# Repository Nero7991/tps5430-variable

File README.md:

# TPS5430 Variable or VarTPS

This is a DC-DC Buck converter board based on the TPS5430 from TI with both fixed and variable voltage output options, called VarTPS. The board provides four fixed voltage outputs (1.8V, 3.3V, 5V, 12V) selectable via solder jumpers, plus a variable output mode ranging from 1.24V to 32.4V. Variable voltage control is implemented using two 10-turn potentiometers - a 10kΩ potentiometer for coarse adjustment and a 1kΩ potentiometer for fine adjustment, providing approximately 3mV resolution at low voltages. The design includes reverse polarity protection, overcurrent protection via polyfuse, and accepts input and output throught screw terminals.

## Features

* V<sub>in</sub> = 5.5V..36V
* V<sub>in<sub>min</sub></sub> = 1.15 * V<sub>out</sub> (see Datasheet Section 8.2.1.2.8.1)
* V<sub>in<sub>max</sub></sub> = 8.33 * (V<sub>out</sub> + 0.5) (see Datasheet Section 8.2.1.2.8.1)
* V<sub>out</sub> = 1.8V/3.3V/5V/12V (choose via solder bridge)
* Variable voltage out, adjusted using two 10 turn pot with course and fine adjustments. V<sub>out<sub>adjust</sub></sub> = 1.24V..32.4V (choosen via solder bridge)
* Reverse polarity protection with AO3401A p-MOSFET
* 3A (hold)/6A (trip) polyfuse input protection
* The board can be powered with a 2.1mm/5.5mm "standard" Arduino compatible barrel jack connector.
* Status LED

## Schematic

The design was modified in [KiCAD 9](https://www.kicad.org/) from Max Stabel's [TPS5430 on GitHub](https://github.com/M4a1x/TPS5430) and follows the [TPS5430 datasheet (Section 8.2.1)](https://www.ti.com/lit/ds/symlink/tps5430.pdf) reasonably close in the schmatic as well as the layout (Section 10.2).

Deviations are:

* 2x 100uF tantalum capacitors instead of 1x 220uF, since those are basic parts at JLCPCB
* As suggested a 10uF output bypass capacitor is added
* 4x 10uF input capacitors instead of only 1x
* Multiple output voltage options through increased Inductor (47uH instead of 15uH) and solder jumpers. All outputs should work with the full 3A

## License

Licensed under CERN-OHL-S v2 or any later version. See `LICENSE` for more information.

## Contact

Oren Collaco - [https://orencollaco.com/](https://orencollaco.com) - orencollaco97@gmail.com

Project Link: [https://github.com/Nero7991/tps5430-variable](https://github.com/Nero7991/tps5430-variable)

## Acknowledgements

* [Max Stabel](https://max.stabel.family/), [TPS5430 on GitHub](https://github.com/M4a1x/TPS5430)

* [Philip Salamony](https://philsal.co.uk/) and his [BananaSchplit Project](https://github.com/pms67/BananaSchplit) and [Video](https://www.youtube.com/watch?v=qXWYXxDokv4)
* [ugurozkan52/TPS5430_Power_Module](https://github.com/ugurozkan52/TPS5430_Power_Module) which inspired me to add the output voltage jumpers

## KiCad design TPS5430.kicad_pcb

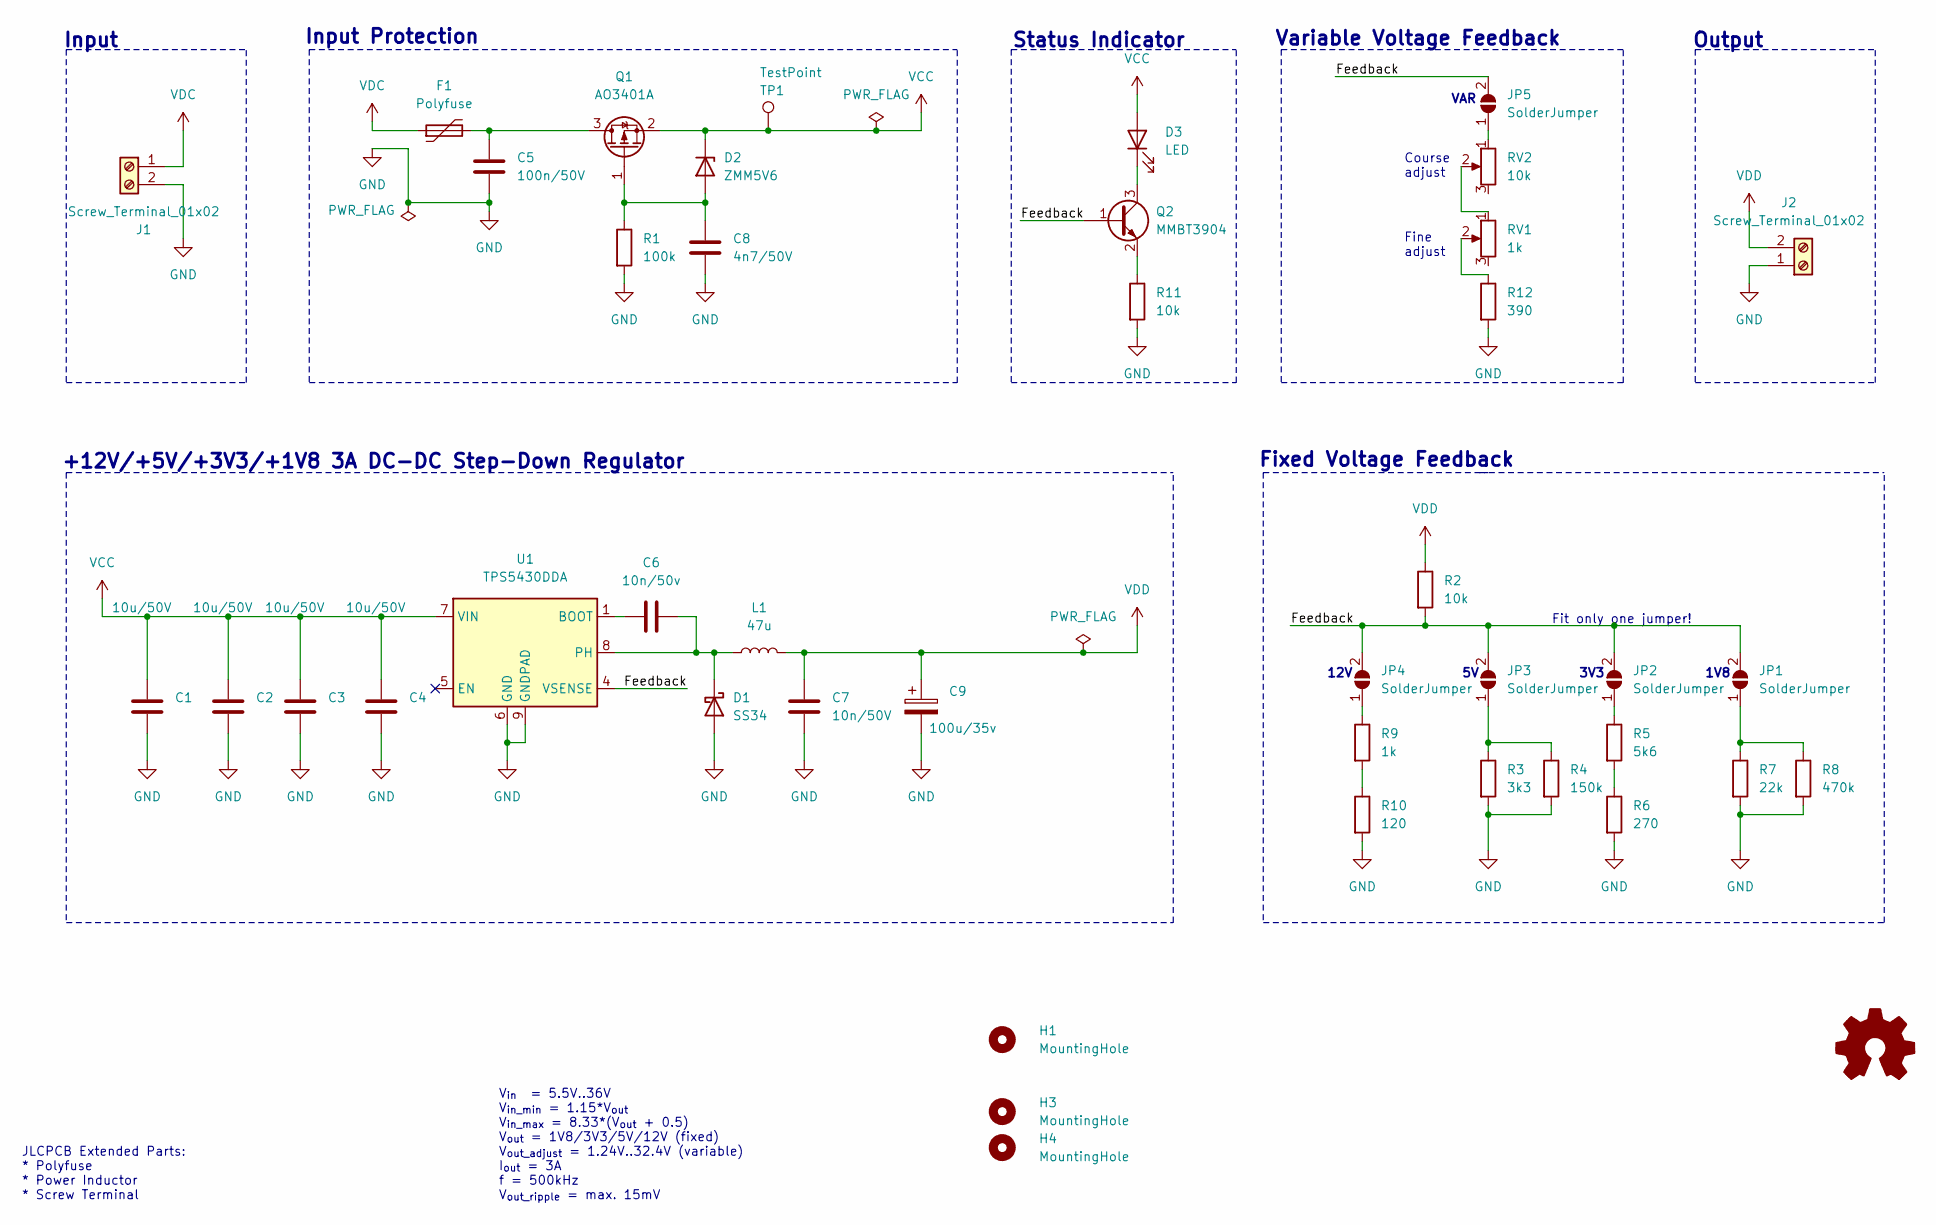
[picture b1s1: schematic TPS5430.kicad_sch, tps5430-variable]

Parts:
C1, C2, C3, C4: 10u/50V; C_1206_3216Metric; MPN CL31A106KBHNNNE; LCSC C13585
C5: 100n/50V; C_0603_1608Metric; MPN CC0603KRX7R9BB104; LCSC C14663
C6: 10n/50v; C_0402_1005Metric; MPN CL05B103KB5NNNC; LCSC C15195
C7: 10n/50V; C_0402_1005Metric; MPN CL05A106MQ5NUNC; LCSC C15525
C8: 4n7/50V; C_0402_1005Metric; MPN 0402B472K500NT; LCSC C1538
C9: 100u/35v; CP_EIA-7343-43_Kemet-X; MPN TAJB107K006RNJ; LCSC C16133
D1: SS34; D_SMA; MPN SS34; LCSC C8678
D2: ZMM5V6; D_MiniMELF; MPN ZMM5V6; LCSC C8062
D3: LED; LED_0603_1608Metric; MPN 19-217/GHC-YR1S2/3T; LCSC C72043
F1: Polyfuse; Fuse_1206_3216Metric; MPN 1206L300SLTHYR; LCSC C207041
H1, H3, H4: MountingHole; MountingHole_2.2mm_M2_ISO7380
J1, J2: Screw_Terminal_01x02; TerminalBlock_Phoenix_PT-1,5-2-3.5-H_1x02_P3.50mm_Horizontal; MPN XY302V-3.5-2P; LCSC C784940
JP1, JP2, JP3, JP4, JP5: SolderJumper; SolderJumper-2_P1.3mm_Open_RoundedPad1.0x1.5mm
L1: 47u; L_Sunlord_MWSA1004S_10x11.5x4mm; MPN MWSA1004S-470MT; LCSC C408491
LOGO1: Logo_Open_Hardware_Small; OSHW-Logo_11.4x12mm_Copper
Q1: AO3401A; SOT-23; MPN AO3401A; LCSC C15127
Q2: MMBT3904; SOT-23; MPN MMBT3904; LCSC C20526
R1: 100k; R_0402_1005Metric; MPN 0402WGF1003TCE; LCSC C25741
R2: 10k; R_0402_1005Metric; MPN 0402WGF1002TCE; LCSC C25744
R3: 3k3; R_0402_1005Metric; MPN 0402WGF3301TCE; LCSC C25890
R4: 150k; R_0402_1005Metric; MPN 0402WGF1503TCE; LCSC C25755
R5: 5k6; R_0402_1005Metric; MPN 0402WGF5601TCE; LCSC C25908
R6: 270; R_0603_1608Metric; MPN 0603WAF2700T5E; LCSC C22966
R7: 22k; R_0402_1005Metric; MPN 0402WGF2202TCE; LCSC C25768
R8: 470k; R_0402_1005Metric; MPN 0402WGF4703TCE; LCSC C25790
R9: 1k; R_0402_1005Metric; MPN 0402WGF1001TCE; LCSC C11702
R10: 120; R_0402_1005Metric; MPN 0402WGF1200TCE; LCSC C25079
R11: 10k; R_0603_1608Metric; MPN 0603WAF1002T5E; LCSC C25804
R12: 390; R_0603_1608Metric; MPN 0603WAF2700T5E; LCSC C22966
RV1: 1k; Potentiometer_Bourns_3296W_Vertical
RV2: 10k; Potentiometer_Bourns_3296W_Vertical
TP1: TestPoint; TestPoint_Pad_D1.0mm
U1: TPS5430DDA; TI_SO-PowerPAD-8_ThermalVias; MPN TPS5430DDAR; JLC LSOP-8_EP_3.9x4.9x1.27P

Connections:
/Feedback: JP1.2 (B), JP2.2 (B), JP3.2 (B), JP4.2 (B), JP5.2 (B), Q2.1 (B), R2.2, U1.4 (VSENSE)
GND: C1.2, C2.2, C3.2, C4.2, C5.2, C7.2, C8.2, C9.2, D1.2 (A), J1.2, J2.1, R1.2, R3.2, R4.2, R6.2, R7.2, R8.2, R10.2, R11.2, R12.2, U1.6 (GND), U1.9 (GNDPAD); also elsewhere on the board
unnamed: C6.2, D1.1 (K), L1.1, U1.8 (PH)
unnamed: C8.1, D2.2 (A), Q1.1 (G), R1.1
unnamed: D3.1 (K), Q2.3 (C)
unnamed: JP1.1 (A), R7.1, R8.1
unnamed: JP2.1 (A), R5.1
unnamed: JP3.1 (A), R3.1, R4.1
unnamed: JP4.1 (A), R9.1
unnamed: JP5.1 (A), RV2.1
unnamed: C5.1, F1.2, Q1.3 (D)
unnamed: Q2.2 (E), R11.1
unnamed: R5.2, R6.1
unnamed: R9.2, R10.1
unnamed: R12.1, RV1.2
unnamed: RV1.1, RV2.2
unnamed: C6.1, U1.1 (BOOT)
VCC: C1.1, C2.1, C3.1, C4.1, D2.1 (K), D3.2 (A), Q1.2 (S), TP1.1, U1.7 (VIN)
VDC: F1.1, J1.1
VDD: C7.1, C9.1, J2.2, L1.2, R2.1; also elsewhere on the board

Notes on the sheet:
Fit only one jumper!
Output
1V8
Input
Course adjust
Status Indicator
JLCPCB Extended Parts: * Polyfuse * Power Inductor * Screw Terminal
Fixed Voltage Feedback
3V3
12V
VAR
Input Protection
+12V/+5V/+3V3/+1V8 3A DC-DC Step-Down Regulator
V_{in} = 5.5V..36V V_{in_min} = 1.15*V_{out} V_{in_max} = 8.33*(V_{out} + 0.5) V_{out} = 1V8/3V3/5V/12V (fixed) V_{out_adjust} = 1.24V..32.4V (variable) I_{out} = 3A f = 500kHz V_{out_ripple} = max. 15mV
Variable Voltage Feedback
Fine adjust

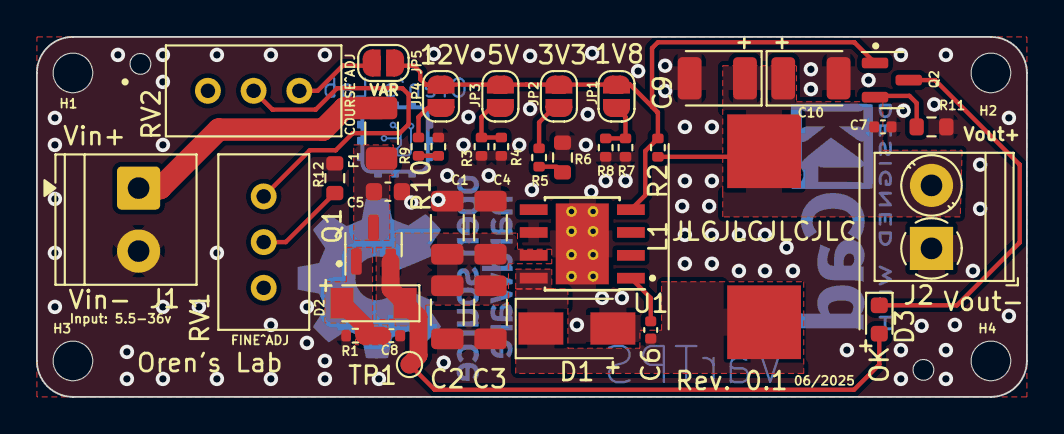
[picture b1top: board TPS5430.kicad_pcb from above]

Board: 2 copper layers, 55.0 x 20.0 mm, 46 parts (1 on the bottom side), 20 nets.

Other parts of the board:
C10: 100u/6.3V; CP_EIA-3528-21_Kemet-B
H2: MountingHole; MountingHole_2.2mm_M2_ISO7380
Logo: LOGO; Orens_Lab_Logo_5x5mm.kicad_sym

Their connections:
GND: C10.2; also elsewhere on the board
VDD: C10.1; also elsewhere on the board

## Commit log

2025-06-27 Initial addition of variable feedback block
2025-06-28 Finished variable feedback block
2025-06-30 Completed placement and routing; Updated REAMME and docs
2025-11-16 printed PCB updates
